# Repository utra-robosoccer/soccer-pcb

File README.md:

TODO's
  - SPI com between mcus
  - validate pinout with firmware
  -

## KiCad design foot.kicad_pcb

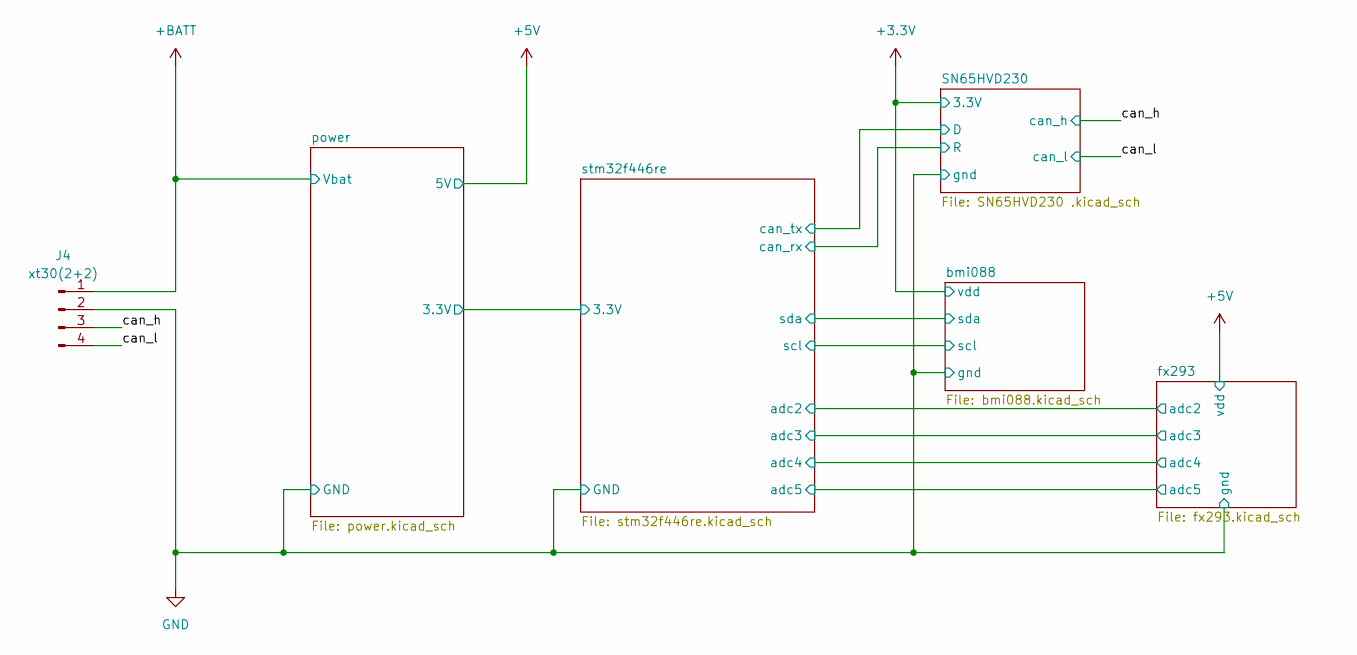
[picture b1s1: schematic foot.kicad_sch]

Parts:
J4: xt30(2+2); xt30pb(2+2)

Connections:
+BATT: J4.1; also elsewhere on the board
/can_h: J4.3; also elsewhere on the board
/can_l: J4.4; also elsewhere on the board
GND: J4.2; also elsewhere on the board

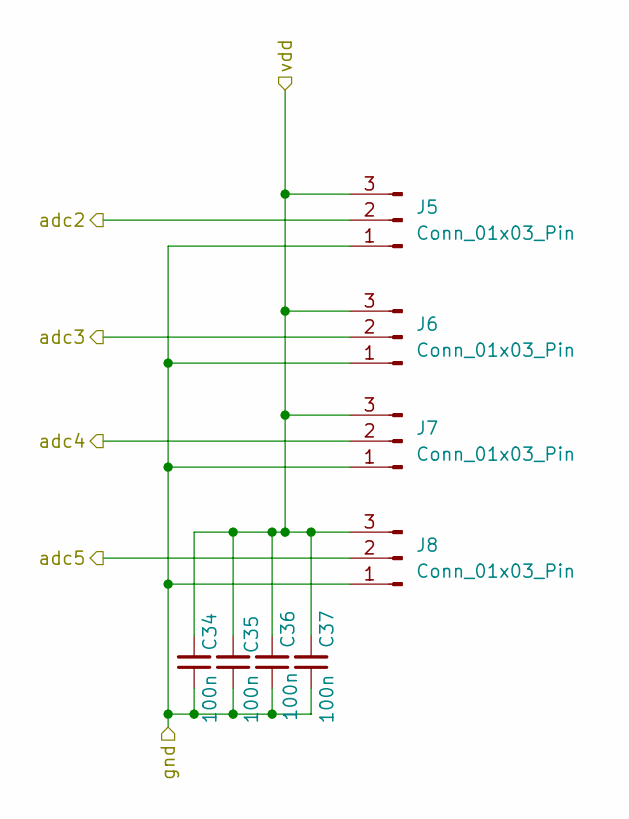
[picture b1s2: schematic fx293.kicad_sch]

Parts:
C34, C35, C36, C37: 100n; C_0402_1005Metric
J5, J6, J7, J8: Conn_01x03_Pin; JST_GH_SM03B-GHS-TB_1x03-1MP_P1.25mm_Horizontal

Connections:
+5V: C34.2, C35.2, C36.2, C37.2, J5.3, J6.3, J7.3, J8.3; also elsewhere on the board
/fx293/adc2: J5.2; also elsewhere on the board
/fx293/adc3: J6.2; also elsewhere on the board
/fx293/adc4: J7.2; also elsewhere on the board
/fx293/adc5: J8.2; also elsewhere on the board
GND: C34.1, C35.1, C36.1, C37.1, J5.1, J6.1, J7.1, J8.1; also elsewhere on the board

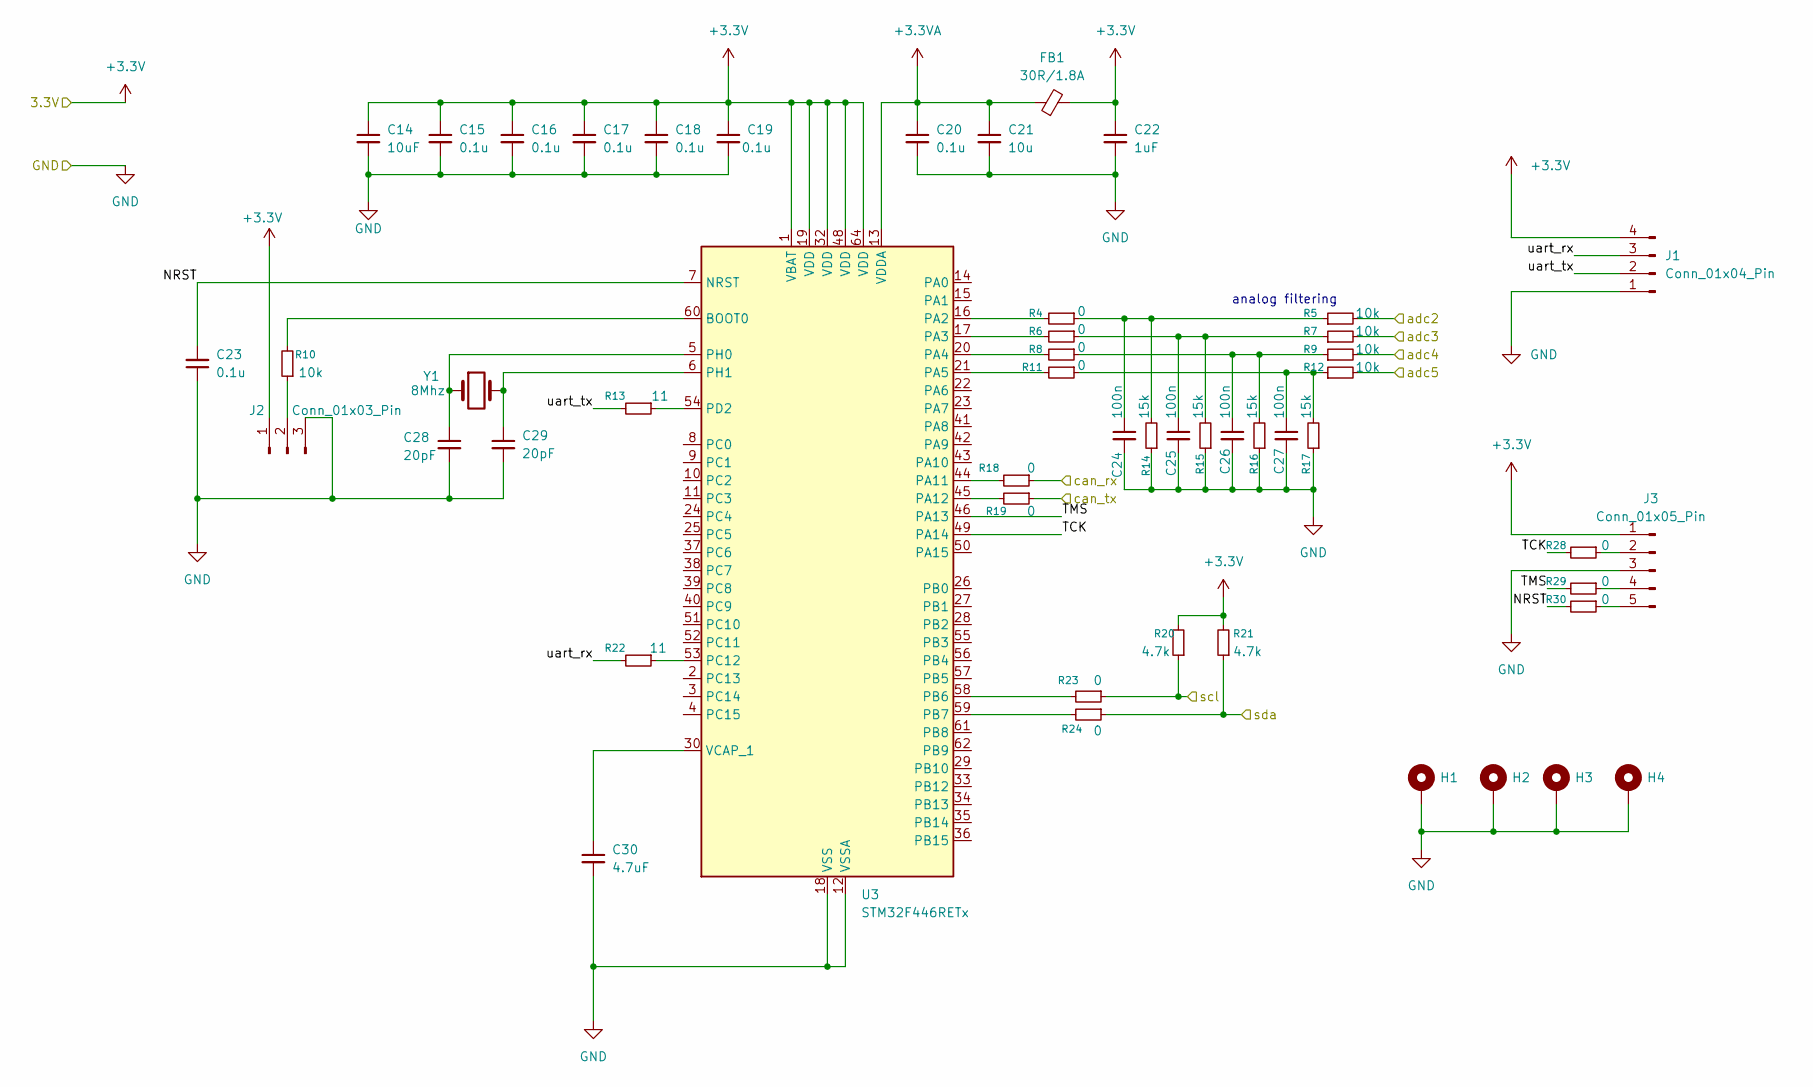
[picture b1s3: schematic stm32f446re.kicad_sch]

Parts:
C14: 10uF; C_0402_1005Metric
C15, C16, C17, C18, C19, C20, C23: 0.1u; C_0402_1005Metric
C21: 10u; C_0402_1005Metric
C22: 1uF; C_0402_1005Metric
C24, C25, C26, C27: 100n; C_0402_1005Metric
C28, C29: 20pF; C_0402_1005Metric
C30: 4.7uF; C_0603_1608Metric
FB1: 30R/1.8A; L_0603_1608Metric
H1, H2, H3, H4: MountingHole_Pad; MountingHole_2.7mm_M2.5_DIN965_Pad
J1: Conn_01x04_Pin; PinHeader_1x04_P2.54mm_Vertical
J2: Conn_01x03_Pin; PinHeader_1x03_P2.54mm_Vertical
J3: Conn_01x05_Pin; PinHeader_1x05_P2.54mm_Vertical
R4, R6, R8, R11, R23, R24: 0; R_0402_1005Metric
R5, R7, R9, R10, R12: 10k; R_0402_1005Metric
R13, R22: 11; R_0402_1005Metric
R14, R15, R16, R17: 15k; R_0402_1005Metric
R18, R19, R28, R29, R30: 0; R_0603_1608Metric
R20, R21: 4.7k; R_0402_1005Metric
U3: STM32F446RETx; LQFP-64_10x10mm_P0.5mm
Y1: 8Mhz; Crystal_HC49-U_Vertical

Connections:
+3.3V: C14.1, C15.1, C16.1, C17.1, C18.1, C19.1, C22.1, FB1.2, J1.4, J2.1, J3.1, R20.2, R21.2, U3.1 (VBAT), U3.19 (VDD), U3.32 (VDD), U3.48 (VDD), U3.64 (VDD); also elsewhere on the board
+3.3VA: C20.1, C21.1, FB1.1, U3.13 (VDDA)
/SN65HVD230/D: R19.1; also elsewhere on the board
/SN65HVD230/R: R18.1; also elsewhere on the board
/bmi088/scl: R20.1, R23.1; also elsewhere on the board
/bmi088/sda: R21.1, R24.1; also elsewhere on the board
/fx293/adc2: R5.2; also elsewhere on the board
/fx293/adc3: R7.2; also elsewhere on the board
/fx293/adc4: R9.2; also elsewhere on the board
/fx293/adc5: R12.2; also elsewhere on the board
/stm32f446re/NRST: C23.2, R30.2, U3.7 (NRST)
/stm32f446re/TCK: R28.2, U3.49 (PA14)
/stm32f446re/TMS: R29.2, U3.46 (PA13)
/stm32f446re/uart_rx: J1.3, R22.2
/stm32f446re/uart_tx: J1.2, R13.2
GND: C14.2, C15.2, C16.2, C17.2, C18.2, C19.2, C20.2, C21.2, C22.2, C23.1, C24.2, C25.2, C26.2, C27.2, C28.2, C29.2, C30.2, H1.1, H2.1, H3.1, H4.1, J1.1, J2.3, J3.3, R14.1, R15.1, R16.1, R17.1, U3.12 (VSSA), U3.18 (VSS), U3.31 (VSS), U3.47 (VSS), U3.63 (VSS); also elsewhere on the board
unnamed: C24.1, R4.1, R5.1, R14.2
unnamed: C25.1, R6.1, R7.1, R15.2
unnamed: C26.1, R8.1, R9.1, R16.2
unnamed: C27.1, R11.1, R12.1, R17.2
unnamed: J2.2, R10.1
unnamed: J3.2, R28.1
unnamed: J3.4, R29.1
unnamed: J3.5, R30.1
unnamed: R10.2, U3.60 (BOOT0)
unnamed: R4.2, U3.16 (PA2)
unnamed: R6.2, U3.17 (PA3)
unnamed: R8.2, U3.20 (PA4)
unnamed: R11.2, U3.21 (PA5)
unnamed: R18.2, U3.44 (PA11)
unnamed: R19.2, U3.45 (PA12)
unnamed: R23.2, U3.58 (PB6)
unnamed: R24.2, U3.59 (PB7)
unnamed: R22.1, U3.53 (PC12)
unnamed: R13.1, U3.54 (PD2)
unnamed: C28.1, U3.5 (PH0), Y1.1
unnamed: C29.1, U3.6 (PH1), Y1.2
unnamed: C30.1, U3.30 (VCAP_1)

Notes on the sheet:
analog filtering

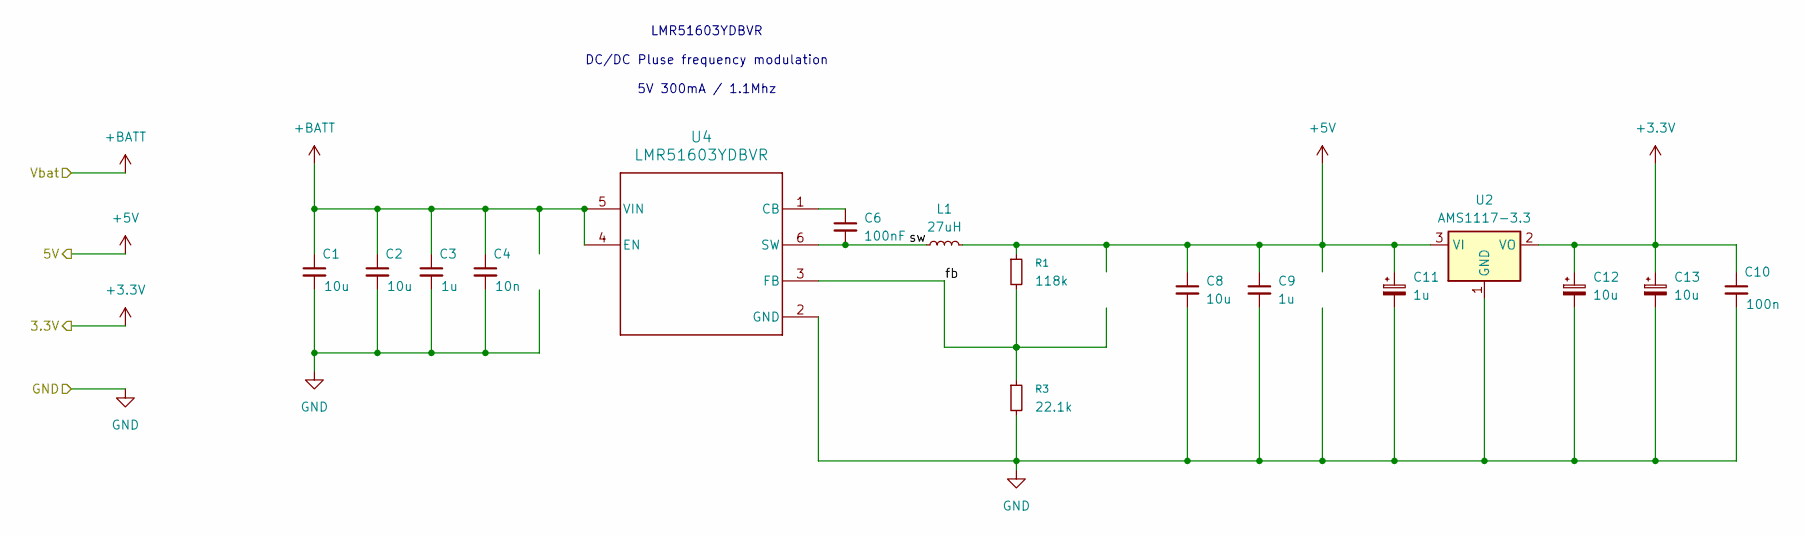
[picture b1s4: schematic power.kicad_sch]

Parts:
C1, C2, C8: 10u; C_1206_3216Metric
C3, C9: 1u; C_1206_3216Metric
C4: 10n; C_0603_1608Metric
C6: 100nF; C_0603_1608Metric
C10: 100n; C_0603_1608Metric
C11: 1u; CP_EIA-3216-18_Kemet-A
C12, C13: 10u; CP_EIA-3216-18_Kemet-A
L1: 27uH; IND_ASPI-0428S-270M-T
R1: 118k; R_0402_1005Metric
R3: 22.1k; R_0402_1005Metric
U2: AMS1117-3.3; SOT-223-3_TabPin2
U4: LMR51603YDBVR; TSOT-23-6

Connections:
+3.3V: C10.1, C12.1, C13.1, U2.2 (VO); also elsewhere on the board
+5V: C8.1, C9.1, C11.1, L1.2, R1.1, U2.3 (VI); also elsewhere on the board
+BATT: C1.1, C2.1, C3.1, C4.1, U4.4 (EN), U4.5 (VIN); also elsewhere on the board
/power/fb: R1.2, R3.1, U4.3 (FB)
/power/sw: C6.2, L1.1, U4.6 (SW)
GND: C1.2, C2.2, C3.2, C4.2, C8.2, C9.2, C10.2, C11.2, C12.2, C13.2, R3.2, U2.1 (GND), U4.2 (GND); also elsewhere on the board
unnamed: C6.1, U4.1 (CB)

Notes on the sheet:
LMR51603YDBVR DC/DC Pluse frequency modulation 5V 300mA / 1.1Mhz

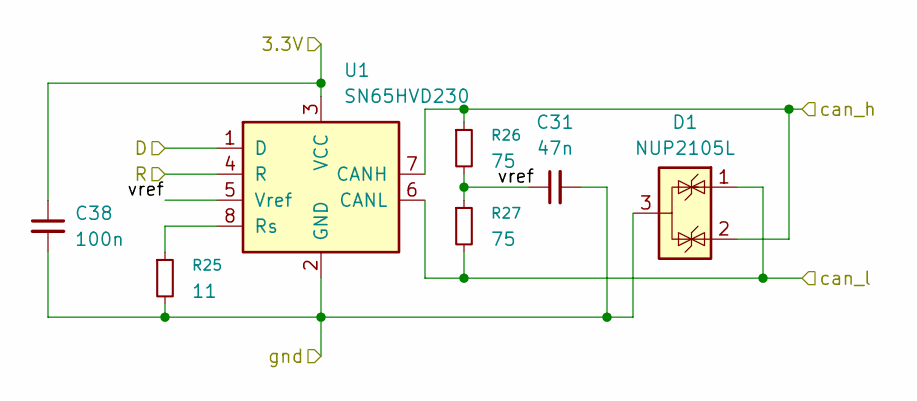
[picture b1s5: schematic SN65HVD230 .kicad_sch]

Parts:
C31: 47n; C_0402_1005Metric
C38: 100n; C_0402_1005Metric
D1: NUP2105L; SOT-23
R25: 11; R_0402_1005Metric
R26, R27: 75; R_0402_1005Metric
U1: SN65HVD230; SOIC-8_3.9x4.9mm_P1.27mm

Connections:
+3.3V: C38.1, U1.3 (VCC); also elsewhere on the board
/SN65HVD230/D: U1.1 (D); also elsewhere on the board
/SN65HVD230/R: U1.4 (R); also elsewhere on the board
/SN65HVD230/vref: C31.1, R26.2, R27.1, U1.5 (Vref)
/can_h: D1.2 (K), R26.1, U1.7 (CANH); also elsewhere on the board
/can_l: D1.1 (K), R27.2, U1.6 (CANL); also elsewhere on the board
GND: C31.2, C38.2, D1.3 (A), R25.2, U1.2 (GND); also elsewhere on the board
unnamed: R25.1, U1.8 (Rs)

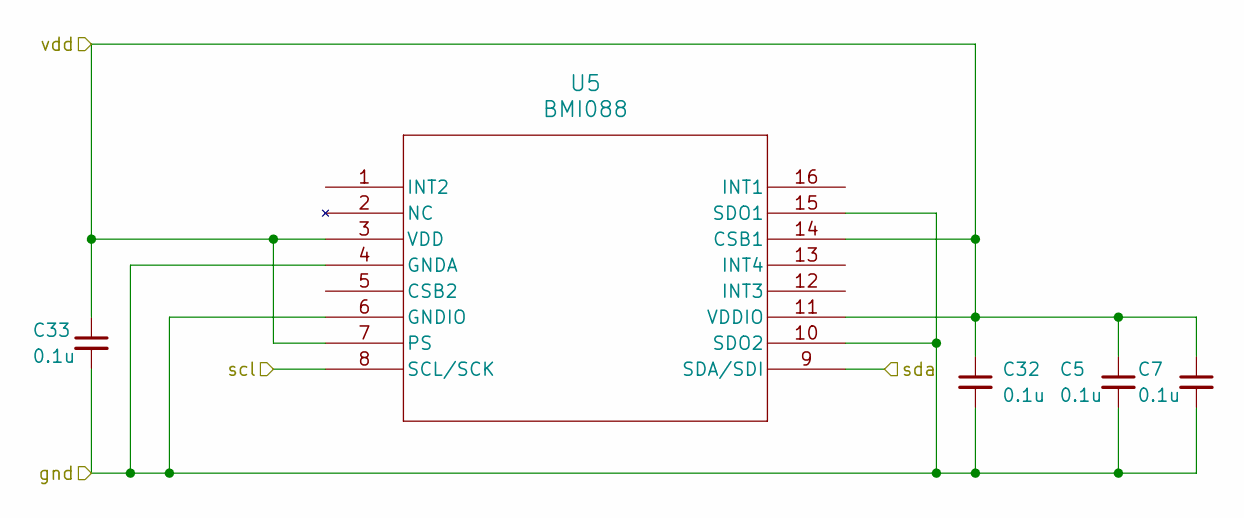
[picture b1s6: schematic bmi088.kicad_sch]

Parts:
C5, C7, C32, C33: 0.1u; C_0402_1005Metric
U5: BMI088; QFN_BMI085_BOS

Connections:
+3.3V: C5.1, C7.1, C32.1, C33.1, U5.3 (VDD), U5.7 (PS), U5.11 (VDDIO), U5.14 (CSB1); also elsewhere on the board
/bmi088/scl: U5.8 (SCL/SCK); also elsewhere on the board
/bmi088/sda: U5.9 (SDA/SDI); also elsewhere on the board
GND: C5.2, C7.2, C32.2, C33.2, U5.4 (GNDA), U5.6 (GNDIO), U5.10 (SDO2), U5.15 (SDO1); also elsewhere on the board

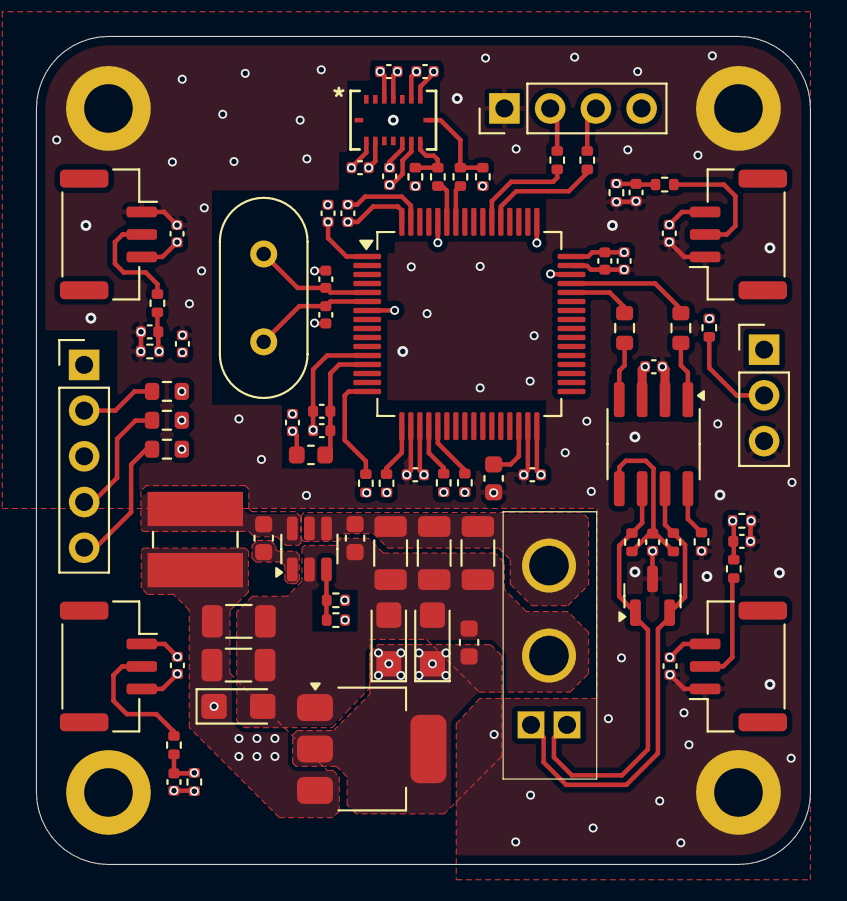
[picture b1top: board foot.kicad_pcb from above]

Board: 6 copper layers, 43.0 x 46.0 mm, 88 parts (0 on the bottom side), 47 nets.

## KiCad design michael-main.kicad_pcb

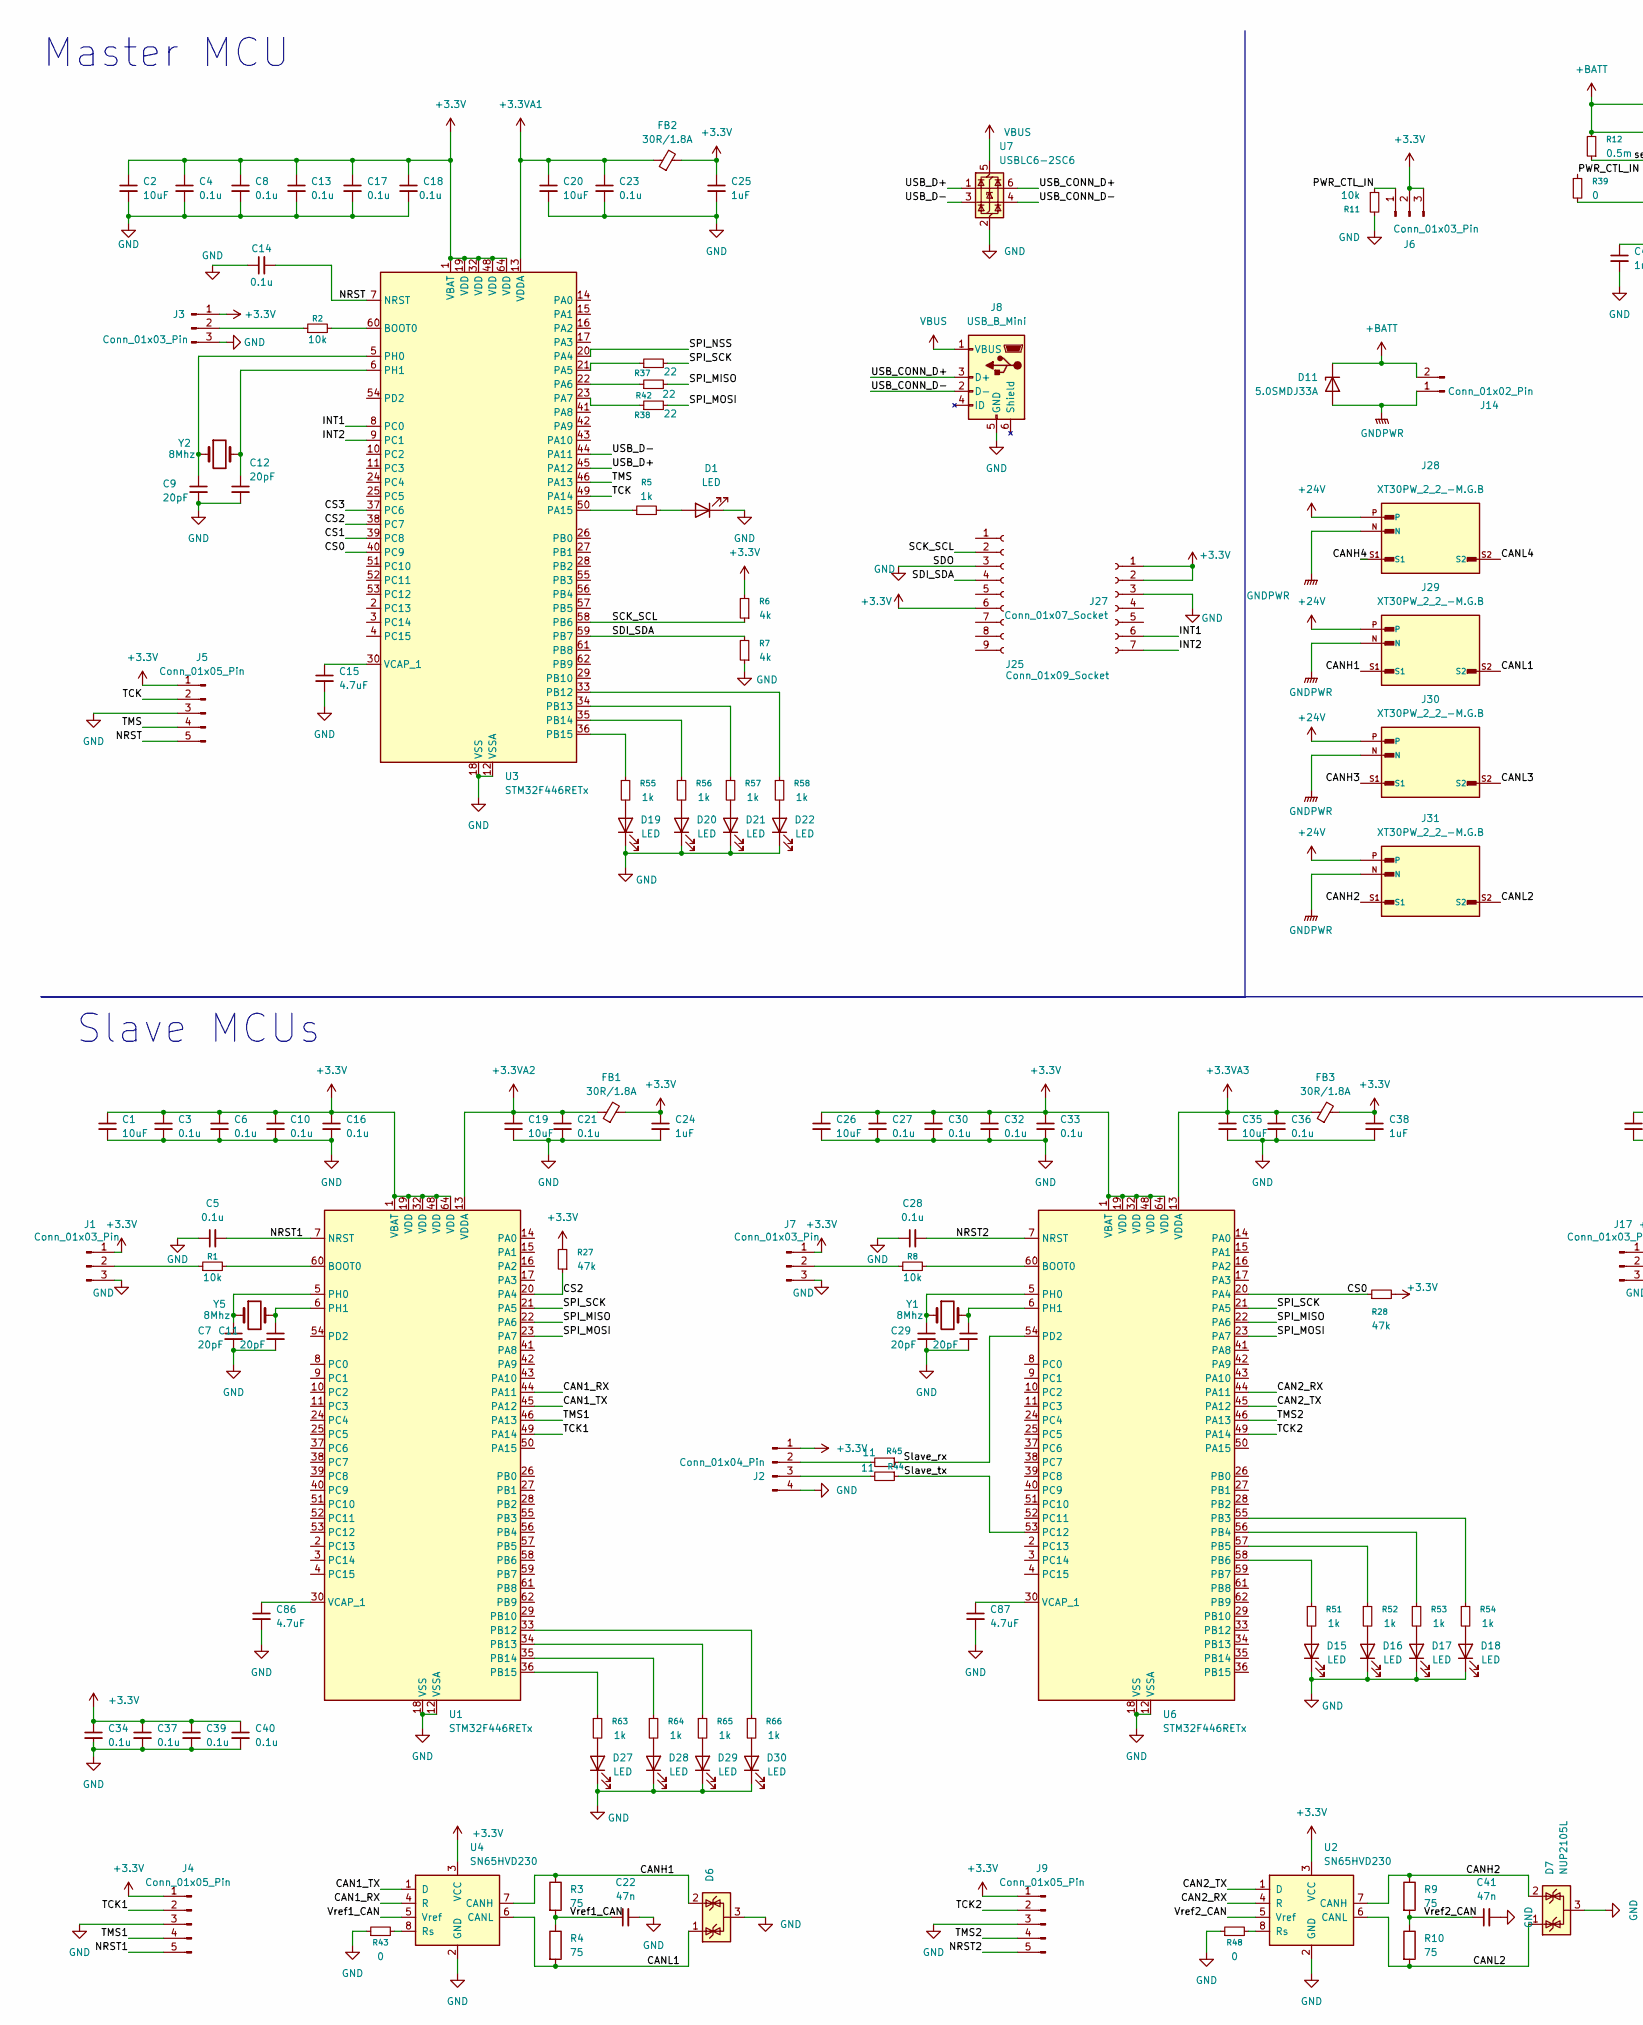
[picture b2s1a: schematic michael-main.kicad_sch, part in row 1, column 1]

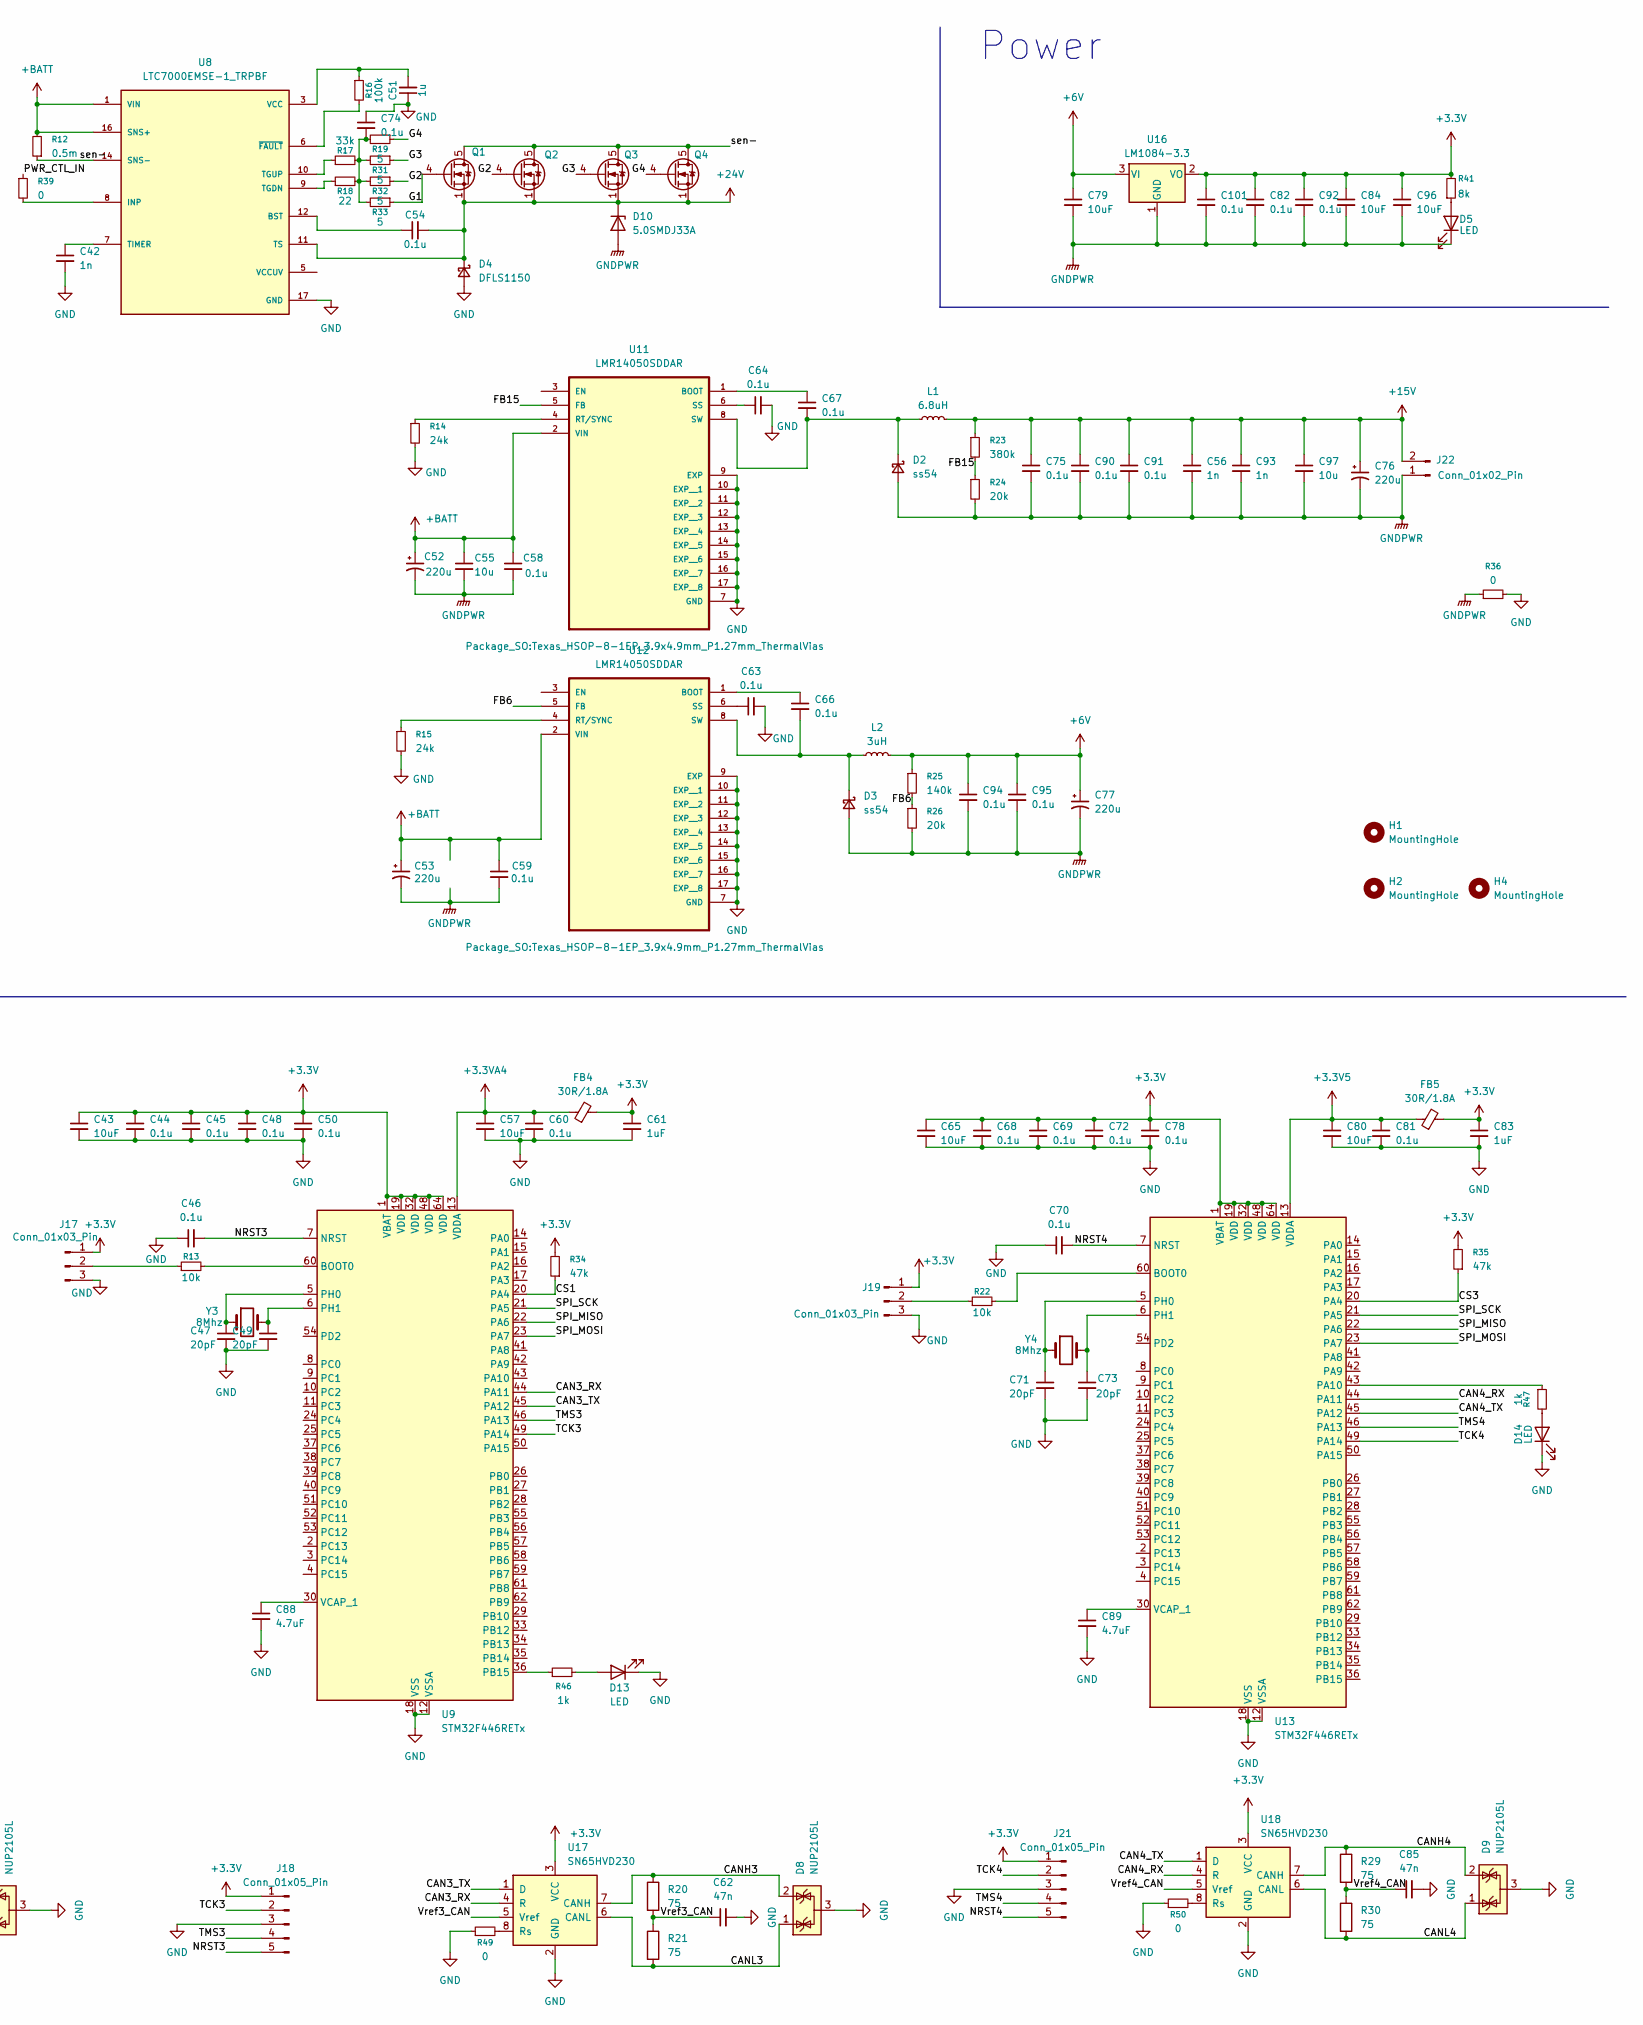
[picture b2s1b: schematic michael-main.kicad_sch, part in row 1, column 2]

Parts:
C1, C2, C19, C20, C26, C35, C43, C57, C65, C80: 10uF; C_0402_1005Metric
C3, C4, C5, C6, C8, C10, C13, C14, C16, C17, C18, C21, C23, C27, C28, C30, C32, C33, C34, C36, C37, C39, C40, C44, C45, C46, C48, C50, C60, C68, C69, C70, C72, C78, C81: 0.1u; C_0402_1005Metric
C7, C9, C11, C12, C29, C31, C47, C49, C71, C73: 20pF; C_0603_1608Metric
C15: 4.7uF; C_0603_1608Metric
C22, C41, C62, C85: 47n; C_0603_1608Metric
C24, C25, C38, C61, C83: 1uF; C_0402_1005Metric
C42: 1n; C_0603_1608Metric
C51: 1u; C_0603_1608Metric
C52, C53, C76, C77: 220u; C_Elec_6.3x7.7
C54, C58, C59, C63, C64, C66, C67, C74, C75, C82, C90, C91, C92, C94, C95, C101: 0.1u; C_0805_2012Metric
C55, C97: 10u; C_0805_2012Metric
C56, C93: 1n; C_0805_2012Metric
C79: 10uF; C_1206_3216Metric
C84, C96: 10uF; C_0805_2012Metric
C86, C87, C88, C89: 4.7uF; C_0402_1005Metric
D1, D5, D13, D14, D15, D16, D17, D18, D19, D20, D21, D22, D27, D28, D29, D30: LED; LED_0603_1608Metric
D2, D3: ss54; D_SMB
D4: DFLS1150; D_PowerDI-123
D6, D7, D8, D9: NUP2105L; SOT-23
D10, D11: 5.0SMDJ33A; D_SMC
FB1, FB2, FB3, FB4, FB5: 30R/1.8A; L_0603_1608Metric
H1, H2, H4: MountingHole; MountingHole_2.2mm_M2
J1, J3, J7, J17, J19: Conn_01x03_Pin; PinHeader_1x03_P2.54mm_Vertical
J2: Conn_01x04_Pin; PinHeader_1x04_P2.54mm_Vertical
J4, J5, J9, J18, J21: Conn_01x05_Pin; PinHeader_1x05_P2.54mm_Vertical
J6: Conn_01x03_Pin; JST_XH_B3B-XH-A_1x03_P2.50mm_Vertical
J8: USB_B_Mini; USB_MINI
J14: Conn_01x02_Pin; AMASS_XT60PW-M_1x02_P7.20mm_Horizontal
J22: Conn_01x02_Pin; AMASS_XT60-M_1x02_P7.20mm_Vertical
J25: Conn_01x09_Socket; PinSocket_1x09_P1.27mm_Vertical
J27: Conn_01x07_Socket; PinSocket_1x07_P1.27mm_Vertical
J28, J29, J30, J31: XT30PW_2_2_-M.G.B; AMASS_XT30PW_2_2_-M.G.B; PARTREV NA
L1: 6.8uH; L_SXN_SMDRI124
L2: 3uH; L_Changjiang_FNR8040S
Q1, Q2, Q3, Q4: BSC340N08NS3G; TDSON-8-1
R1, R2, R8, R11, R13, R22: 10k; R_0402_1005Metric
R3, R4, R9, R10, R20, R21, R29, R30: 75; R_0603_1608Metric
R5, R46, R47, R51, R52, R53, R54, R55, R56, R57, R58, R63, R64, R65, R66: 1k; R_0603_1608Metric
R6, R7: 4k; R_0603_1608Metric
R12: 0.5m; RES_WSLP3921_.001OHM_VIS-L
R14, R15: 24k; R_0805_2012Metric
R16: 100k; R_0603_1608Metric
R17: 33k; R_0805_2012Metric
R18: 22; R_0805_2012Metric
R19, R31, R32, R33: 5; R_0805_2012Metric
R23: 380k; R_0805_2012Metric
R24, R26: 20k; R_0805_2012Metric
R25: 140k; R_0805_2012Metric
R27, R28, R34, R35: 47k; R_0402_1005Metric
R36: 0; R_0805_2012Metric
R37, R38, R42: 22; R_0603_1608Metric
R39: 0; R_0402_1005Metric
R41: 8k; R_0603_1608Metric
R43, R48, R49, R50: 0; R_0603_1608Metric
R44, R45: 11; R_0603_1608Metric
U1, U3, U6, U9, U13: STM32F446RETx; LQFP-64_10x10mm_P0.5mm
U2, U4, U17, U18: SN65HVD230; SOIC-8_3.9x4.9mm_P1.27mm
U7: USBLC6-2SC6; SOT-23-6
U8: LTC7000EMSE-1_TRPBF; SOP50P490X110-17N; PARTREV F
U11, U12: LMR14050SDDAR; Texas_HSOP-8-1EP_3.9x4.9mm_P1.27mm_ThermalVias
U16: LM1084-3.3; TO-263-3_TabPin2
Y1, Y2, Y3, Y4, Y5: 8Mhz; Crystal_HC49-U_Vertical

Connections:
+3.3V: C1.1, C2.1, C3.1, C4.1, C6.1, C8.1, C10.1, C13.1, C16.1, C17.1, C18.1, C24.1, C25.1, C26.1, C27.1, C30.1, C32.1, C33.1, C34.1, C37.1, C38.1, C39.1, C40.1, C43.1, C44.1, C45.1, C48.1, C50.1, C61.1, C65.1, C68.1, C69.1, C72.1, C78.1, C82.1, C83.1, C84.1, C92.1, C96.1, C101.1, FB1.2, FB2.2, FB3.2, FB4.2, FB5.2, J1.1, J2.1, J3.1, J4.1, J5.1, J6.2, J6.3, J7.1, J9.1, J17.1, J18.1, J19.1, J21.1, J25.6, J27.1, J27.2, R6.2, R27.2, R28.2, R34.2, R35.2, R41.2, U1.1 (VBAT), U1.19 (VDD), U1.32 (VDD), U1.48 (VDD), U1.64 (VDD), U2.3 (VCC), U3.1 (VBAT), U3.19 (VDD), U3.32 (VDD), U3.48 (VDD), U3.64 (VDD), U4.3 (VCC), U6.1 (VBAT), U6.19 (VDD), U6.32 (VDD), U6.48 (VDD), U6.64 (VDD), U9.1 (VBAT), U9.19 (VDD), U9.32 (VDD), U9.48 (VDD), U9.64 (VDD), U13.1 (VBAT), U13.19 (VDD), U13.32 (VDD), U13.48 (VDD), U13.64 (VDD), U16.2 (VO), U17.3 (VCC), U18.3 (VCC); also elsewhere on the board
+3.3V5: C80.1, C81.1, FB5.1, U13.13 (VDDA)
+3.3VA1: C20.1, C23.1, FB2.1, U3.13 (VDDA)
+3.3VA2: C19.1, C21.1, FB1.1, U1.13 (VDDA)
+3.3VA3: C35.1, C36.1, FB3.1, U6.13 (VDDA)
+3.3VA4: C57.1, C60.1, FB4.1, U9.13 (VDDA)
+6V: C77.1, C79.1, C94.1, C95.1, L2.2, R25.1, U16.3 (VI)
+15V: C56.1, C75.1, C76.1, C90.1, C91.1, C93.1, C97.1, J22.2, L1.2, R23.1
+24V: C54.2, D4.1 (K), D10.1 (K), J28.P, J29.P, J30.P, J31.P, Q1.1 (S), Q1.2 (S), Q1.3 (S), Q2.1 (S), Q2.2 (S), Q2.3 (S), Q3.1 (S), Q3.2 (S), Q3.3 (S), Q4.1 (S), Q4.2 (S), Q4.3 (S), U8.11 (TS)
+BATT: C52.1, C53.1, C55.1, C58.1, C59.1, D11.1 (K), J14.2, R12.2, U8.1 (VIN), U8.16 (SNS+), U11.2 (VIN), U12.2 (VIN)
/CAN1_RX: U1.44 (PA11), U4.4 (R)
/CAN1_TX: U1.45 (PA12), U4.1 (D)
/CAN2_RX: U2.4 (R), U6.44 (PA11)
/CAN2_TX: U2.1 (D), U6.45 (PA12)
/CAN3_RX: U9.44 (PA11), U17.4 (R)
/CAN3_TX: U9.45 (PA12), U17.1 (D)
/CAN4_RX: U13.44 (PA11), U18.4 (R)
/CAN4_TX: U13.45 (PA12), U18.1 (D)
/CANH1: D6.2 (K), J29.S1, R3.1, U4.7 (CANH)
/CANH2: D7.2 (K), J31.S1, R9.1, U2.7 (CANH)
/CANH3: D8.2 (K), J30.S1, R20.1, U17.7 (CANH)
/CANH4: D9.2 (K), J28.S1, R29.1, U18.7 (CANH)
/CANL1: D6.1 (K), J29.S2, R4.2, U4.6 (CANL)
/CANL2: D7.1 (K), J31.S2, R10.2, U2.6 (CANL)
/CANL3: D8.1 (K), J30.S2, R21.2, U17.6 (CANL)
/CANL4: D9.1 (K), J28.S2, R30.2, U18.6 (CANL)
/CS0: R28.1, U3.40 (PC9), U6.20 (PA4)
/CS1: R34.1, U3.39 (PC8), U9.20 (PA4)
/CS2: R27.1, U1.20 (PA4), U3.38 (PC7)
/CS3: R35.1, U3.37 (PC6), U13.20 (PA4)
/FB6: R25.2, R26.1, U12.5 (FB)
/FB15: R23.2, R24.1, U11.5 (FB)
/G1: Q1.4 (G), R33.1
/G2: Q2.4 (G), R32.1
/G3: Q3.4 (G), R31.1
/G4: Q4.4 (G), R19.1
/INT1: J27.6, U3.8 (PC0)
/INT2: J27.7, U3.9 (PC1)
/NRST: C14.2, J5.5, U3.7 (NRST)
/NRST1: C5.2, J4.5, U1.7 (NRST)
/NRST2: C28.2, J9.5, U6.7 (NRST)
/NRST3: C46.2, J18.5, U9.7 (NRST)
/NRST4: C70.2, J21.5, U13.7 (NRST)
/PWR_CTL_IN: J6.1, R11.1, R39.1
/SCK_SCL: J25.2, R6.1, U3.58 (PB6)
/SDI_SDA: J25.4, R7.2, U3.59 (PB7)
/SPI_MISO: R42.2, U1.22 (PA6), U6.22 (PA6), U9.22 (PA6), U13.22 (PA6)
/SPI_MOSI: R38.2, U1.23 (PA7), U6.23 (PA7), U9.23 (PA7), U13.23 (PA7)
/SPI_NSS: U3.20 (PA4)
/SPI_SCK: R37.2, U1.21 (PA5), U6.21 (PA5), U9.21 (PA5), U13.21 (PA5)
/Slave_rx: R45.1, U6.54 (PD2)
/Slave_tx: R44.1, U6.53 (PC12)
/TCK: J5.2, U3.49 (PA14)
/TCK1: J4.2, U1.49 (PA14)
/TCK2: J9.2, U6.49 (PA14)
/TCK3: J18.2, U9.49 (PA14)
/TCK4: J21.2, U13.49 (PA14)
/TMS: J5.4, U3.46 (PA13)
/TMS1: J4.4, U1.46 (PA13)
/TMS2: J9.4, U6.46 (PA13)
/TMS3: J18.4, U9.46 (PA13)
/TMS4: J21.4, U13.46 (PA13)
/USB_CONN_D+: J8.3 (D+), U7.6 (I/O1)
/USB_CONN_D-: J8.2 (D-), U7.4 (I/O2)
/USB_D+: U3.45 (PA12), U7.1 (I/O1)
/USB_D-: U3.44 (PA11), U7.3 (I/O2)
/Vref1_CAN: C22.1, R3.2, R4.1, U4.5 (Vref)
/Vref2_CAN: C41.1, R9.2, R10.1, U2.5 (Vref)
/Vref3_CAN: C62.1, R20.2, R21.1, U17.5 (Vref)
/Vref4_CAN: C85.1, R29.2, R30.1, U18.5 (Vref)
/sen-: Q1.5 (D), Q2.5 (D), Q3.5 (D), Q4.5 (D), R12.1, U8.14 (SNS-)
GND: C1.2, C2.2, C3.2, C4.2, C5.1, C6.2, C7.2, C8.2, C9.2, C10.2, C11.2, C12.2, C13.2, C14.1, C15.2, C16.2, C17.2, C18.2, C19.2, C20.2, C21.2, C22.2, C23.2, C24.2, C25.2, C26.2, C27.2, C28.1, C29.2, C30.2, C31.2, C32.2, C33.2, C34.2, C35.2, C36.2, C37.2, C38.2, C39.2, C40.2, C41.2, C42.2, C43.2, C44.2, C45.2, C46.1, C47.2, C48.2, C49.2, C50.2, C51.1, C57.2, C60.2, C61.2, C62.2, C63.2, C64.2, C65.2, C68.2, C69.2, C70.1, C71.2, C72.2, C73.2, C74.1, C78.2, C80.2, C81.2, C83.2, C85.2, C86.2, C87.2, C88.2, C89.2, D1.1 (K), D4.2 (A), D6.3 (A), D7.3 (A), D8.3 (A), D9.3 (A), D13.1 (K), D14.1 (K), D15.1 (K), D16.1 (K), D17.1 (K), D18.1 (K), D19.1 (K), D20.1 (K), D21.1 (K), D22.1 (K), D27.1 (K), D28.1 (K), D29.1 (K), D30.1 (K), J1.3, J2.4, J3.3, J4.3, J5.3, J7.3, J8.5 (GND), J9.3, J17.3, J18.3, J19.3, J21.3, J25.3, J27.3, R7.1, R11.2, R14.2, R15.2, R36.2, R43.1, R48.1, R49.1, R50.1, U1.12 (VSSA), U1.18 (VSS), U1.31 (VSS), U1.47 (VSS), U1.63 (VSS), U2.2 (GND), U3.12 (VSSA), U3.18 (VSS), U3.31 (VSS), U3.47 (VSS), U3.63 (VSS), U4.2 (GND), U6.12 (VSSA), U6.18 (VSS), U6.31 (VSS), U6.47 (VSS), U6.63 (VSS), U7.2 (GND), U8.17 (GND), U9.12 (VSSA), U9.18 (VSS), U9.31 (VSS), U9.47 (VSS), U9.63 (VSS), U11.7 (GND), U11.9 (EXP), U11.10 (EXP__1), U11.11 (EXP__2), U11.12 (EXP__3), U11.13 (EXP__4), U11.14 (EXP__5), U11.15 (EXP__6), U11.16 (EXP__7), U11.17 (EXP__8), U12.7 (GND), U12.9 (EXP), U12.10 (EXP__1), U12.11 (EXP__2), U12.12 (EXP__3), U12.13 (EXP__4), U12.14 (EXP__5), U12.15 (EXP__6), U12.16 (EXP__7), U12.17 (EXP__8), U13.12 (VSSA), U13.18 (VSS), U13.31 (VSS), U13.47 (VSS), U13.63 (VSS), U17.2 (GND), U18.2 (GND)
GNDPWR: C52.2, C53.2, C55.2, C56.2, C58.2, C59.2, C75.2, C76.2, C77.2, C79.2, C82.2, C84.2, C90.2, C91.2, C92.2, C93.2, C94.2, C95.2, C96.2, C97.2, C101.2, D2.2 (A), D3.2 (A), D5.1 (K), D10.2 (A), D11.2 (A), J14.1, J22.1, J28.N, J29.N, J30.N, J31.N, R24.2, R26.2, R36.1, U16.1 (GND)
unnamed: C74.2, R17.2, R18.2, R19.2, R31.2, R32.2, R33.2
unnamed: D1.2 (A), R5.2
unnamed: C67.2, D2.1 (K), L1.1, U11.8 (SW)
unnamed: C66.2, D3.1 (K), L2.1, U12.8 (SW)
unnamed: D5.2 (A), R41.1
unnamed: D13.2 (A), R46.2
unnamed: D14.2 (A), R47.2
unnamed: D15.2 (A), R51.2
unnamed: D16.2 (A), R52.2
unnamed: D17.2 (A), R53.2
unnamed: D18.2 (A), R54.2
unnamed: D19.2 (A), R55.2
unnamed: D20.2 (A), R56.2
unnamed: D21.2 (A), R57.2
unnamed: D22.2 (A), R58.2
unnamed: D27.2 (A), R63.2
unnamed: D28.2 (A), R64.2
unnamed: D29.2 (A), R65.2
unnamed: D30.2 (A), R66.2
unnamed: J1.2, R1.1
unnamed: J2.2, R45.2
unnamed: J2.3, R44.2
unnamed: J3.2, R2.1
unnamed: J7.2, R8.1
unnamed: J17.2, R13.1
unnamed: J19.2, R22.1
unnamed: R1.2, U1.60 (BOOT0)
unnamed: R66.1, U1.33 (PB12)
unnamed: R65.1, U1.34 (PB13)
unnamed: R64.1, U1.35 (PB14)
unnamed: R63.1, U1.36 (PB15)
unnamed: C7.1, U1.5 (PH0), Y5.1
unnamed: C11.1, U1.6 (PH1), Y5.2
unnamed: C86.1, U1.30 (VCAP_1)
unnamed: R48.2, U2.8 (Rs)
unnamed: R2.2, U3.60 (BOOT0)
unnamed: R37.1, U3.21 (PA5)
unnamed: R42.1, U3.22 (PA6)
unnamed: R38.1, U3.23 (PA7)
unnamed: R5.1, U3.50 (PA15)
unnamed: R58.1, U3.33 (PB12)
unnamed: R57.1, U3.34 (PB13)
unnamed: R56.1, U3.35 (PB14)
unnamed: R55.1, U3.36 (PB15)
unnamed: C9.1, U3.5 (PH0), Y2.1
unnamed: C12.1, U3.6 (PH1), Y2.2
unnamed: C15.1, U3.30 (VCAP_1)
unnamed: R43.2, U4.8 (Rs)
unnamed: R8.2, U6.60 (BOOT0)
unnamed: R54.1, U6.55 (PB3)
unnamed: R53.1, U6.56 (PB4)
unnamed: R52.1, U6.57 (PB5)
unnamed: R51.1, U6.58 (PB6)
unnamed: C29.1, U6.5 (PH0), Y1.1
unnamed: C31.1, U6.6 (PH1), Y1.2
unnamed: C87.1, U6.30 (VCAP_1)
unnamed: C54.1, U8.12 (BST)
unnamed 130: R39.2, U8.8 (INP); also elsewhere on the board
unnamed: R18.1, U8.9 (TGDN)
unnamed: R17.1, U8.10 (TGUP)
unnamed: C42.1, U8.7 (TIMER)
unnamed: C51.2, R16.1, U8.3 (VCC)
unnamed: R16.2, U8.6 (~FAULT)
unnamed: R13.2, U9.60 (BOOT0)
unnamed: R46.1, U9.36 (PB15)
unnamed: C47.1, U9.5 (PH0), Y3.1
unnamed: C49.1, U9.6 (PH1), Y3.2
unnamed: C88.1, U9.30 (VCAP_1)
unnamed: C67.1, U11.1 (BOOT)
unnamed: R14.1, U11.4 (RT/SYNC)
unnamed: C64.1, U11.6 (SS)
unnamed: C66.1, U12.1 (BOOT)
unnamed: R15.1, U12.4 (RT/SYNC)
unnamed: C63.1, U12.6 (SS)
unnamed: R22.2, U13.60 (BOOT0)
unnamed: R47.1, U13.43 (PA10)
unnamed: C71.1, U13.5 (PH0), Y4.1
unnamed: C73.1, U13.6 (PH1), Y4.2
unnamed: C89.1, U13.30 (VCAP_1)
unnamed: R49.2, U17.8 (Rs)
unnamed: R50.2, U18.8 (Rs)
VBUS: J8.1 (VBUS), U7.5 (VBUS)

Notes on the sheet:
Power
Slave MCUs
Master MCU
